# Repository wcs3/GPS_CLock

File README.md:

# GPS_CLock

A device that displays time and date on 7-segment displays in ISO8601 format.

Features:
 - Retrieves accurate time from GPS satellites
 - Displays time in compliance with ISO8601
 - Powered from a rechargeable battery for portable usage
 - Charges from a power delivery capable USB Type-C port

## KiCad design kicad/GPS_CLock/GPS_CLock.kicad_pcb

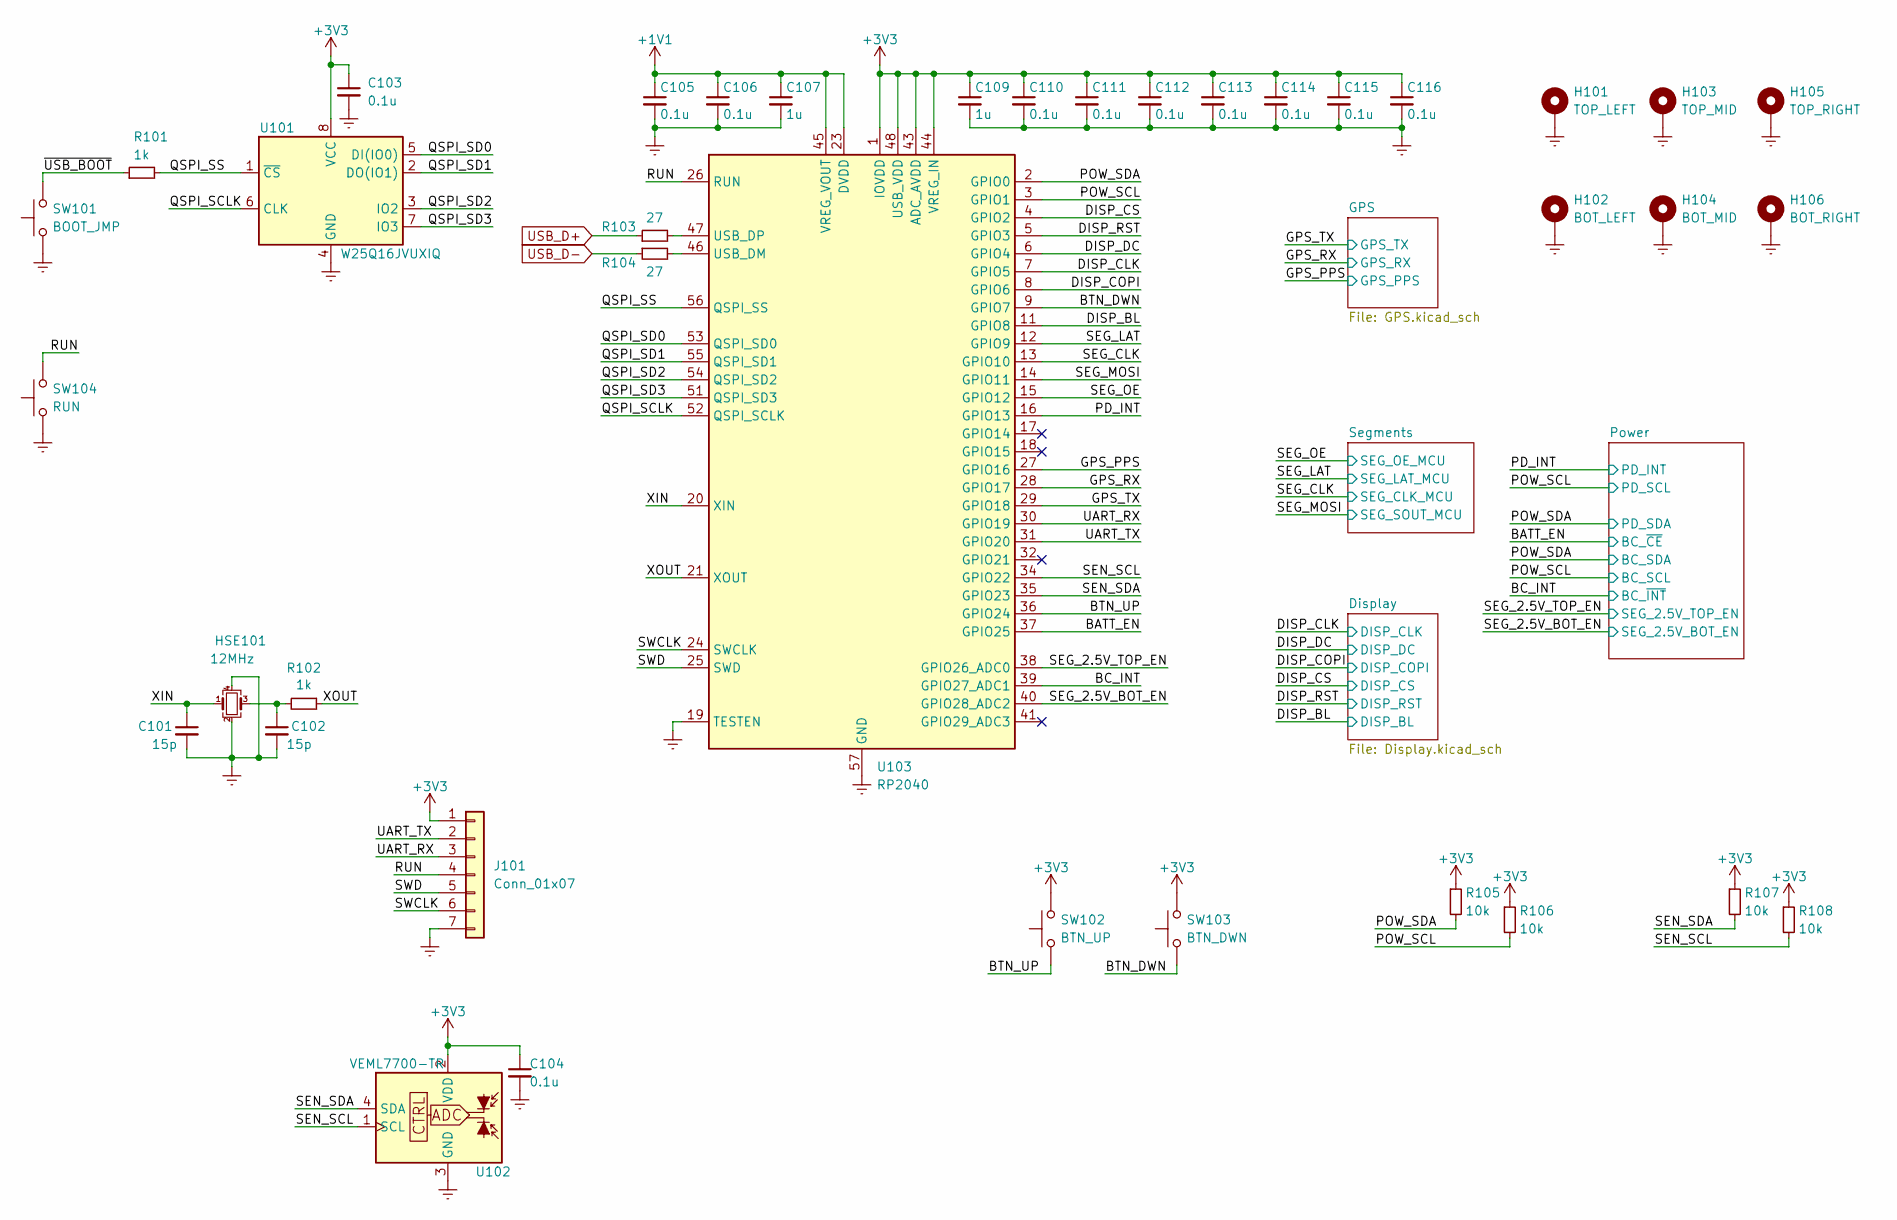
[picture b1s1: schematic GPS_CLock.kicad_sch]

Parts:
C101, C102: 15p; C_0402_1005Metric
C103, C104, C105, C106, C110, C111, C112, C113, C114, C115, C116: 0.1u; C_0402_1005Metric
C107, C109: 1u; C_0402_1005Metric
H101: TOP_LEFT; MountingHole_3.2mm_M3_DIN965_Pad
H102: BOT_LEFT; MountingHole_3.2mm_M3_DIN965_Pad
H103: TOP_MID; MountingHole_3.2mm_M3_DIN965_Pad
H104: BOT_MID; MountingHole_3.2mm_M3_DIN965_Pad
H105: TOP_RIGHT; MountingHole_3.2mm_M3_DIN965_Pad
H106: BOT_RIGHT; MountingHole_3.2mm_M3_DIN965_Pad
HSE101: 12MHz; Crystal_SMD_3225-4Pin_3.2x2.5mm
J101: Conn_01x07; PinHeader_1x07_P1.27mm_Vertical
R101, R102: 1k; R_0402_1005Metric
R103, R104: 27; R_0402_1005Metric
R105, R106, R107, R108: 10k; R_0402_1005Metric
SW101: BOOT_JMP; SW_SPST_EVQP2
SW102: BTN_UP; SW_SPST_EVQP2
SW103: BTN_DWN; SW_SPST_EVQP2
SW104: RUN; SW_SPST_EVQP2
U101: W25Q16JVUXIQ; WINBOND_USON-8_2x3mm
U102: VEML7700-TR; VEML7700
U103: RP2040; QFN-56-1EP_7x7mm_P0.4mm_EP3.2x3.2mm

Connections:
+1V1: C105.1, C106.1, C107.1, U103.23 (DVDD), U103.45 (VREG_VOUT), U103.50 (DVDD)
+3V3: C103.1, C104.1, C109.1, C110.1, C111.1, C112.1, C113.1, C114.1, C115.1, C116.1, J101.1, R105.1, R106.1, R107.1, R108.1, SW102.1, SW103.1, U101.8 (VCC), U102.2 (VDD), U103.1 (IOVDD), U103.10 (IOVDD), U103.22 (IOVDD), U103.33 (IOVDD), U103.42 (IOVDD), U103.43 (ADC_AVDD), U103.44 (VREG_IN), U103.48 (USB_VDD), U103.49 (IOVDD); also elsewhere on the board
/BATT_EN: U103.37 (GPIO25); also elsewhere on the board
/BC_INT: U103.39 (GPIO27_ADC1); also elsewhere on the board
/BTN_DWN: SW103.2, U103.9 (GPIO7)
/BTN_UP: SW102.2, U103.36 (GPIO24)
/DISP_BL: U103.11 (GPIO8); also elsewhere on the board
/DISP_CLK: U103.7 (GPIO5); also elsewhere on the board
/DISP_COPI: U103.8 (GPIO6); also elsewhere on the board
/DISP_CS: U103.4 (GPIO2); also elsewhere on the board
/DISP_DC: U103.6 (GPIO4); also elsewhere on the board
/DISP_RST: U103.5 (GPIO3); also elsewhere on the board
/GPS_PPS: U103.27 (GPIO16); also elsewhere on the board
/GPS_RX: U103.28 (GPIO17); also elsewhere on the board
/GPS_TX: U103.29 (GPIO18); also elsewhere on the board
/PD_INT: U103.16 (GPIO13); also elsewhere on the board
/POW_SCL: R106.2, U103.3 (GPIO1); also elsewhere on the board
/POW_SDA: R105.2, U103.2 (GPIO0); also elsewhere on the board
/QSPI_SCLK: U101.6 (CLK), U103.52 (QSPI_SCLK)
/QSPI_SD0: U101.5 (DI(IO0)), U103.53 (QSPI_SD0)
/QSPI_SD1: U101.2 (DO(IO1)), U103.55 (QSPI_SD1)
/QSPI_SD2: U101.3 (IO2), U103.54 (QSPI_SD2)
/QSPI_SD3: U101.7 (IO3), U103.51 (QSPI_SD3)
/QSPI_SS: R101.2, U101.1 (~CS), U103.56 (QSPI_SS)
/RUN: J101.4, SW104.1, U103.26 (RUN)
/SEG_2.5V_BOT_EN: U103.40 (GPIO28_ADC2); also elsewhere on the board
/SEG_2.5V_TOP_EN: U103.38 (GPIO26_ADC0); also elsewhere on the board
/SEG_CLK: U103.13 (GPIO10); also elsewhere on the board
/SEG_LAT: U103.12 (GPIO9); also elsewhere on the board
/SEG_MOSI: U103.14 (GPIO11); also elsewhere on the board
/SEG_OE: U103.15 (GPIO12); also elsewhere on the board
/SEN_SCL: R108.2, U102.1 (SCL), U103.34 (GPIO22)
/SEN_SDA: R107.2, U102.4 (SDA), U103.35 (GPIO23)
/SWCLK: J101.6, U103.24 (SWCLK)
/SWD: J101.5, U103.25 (SWD)
/UART_RX: J101.3, U103.30 (GPIO19)
/UART_TX: J101.2, U103.31 (GPIO20)
/XIN: C101.1, HSE101.1, U103.20 (XIN)
/XOUT: R102.1, U103.21 (XOUT)
/~USB_BOOT: R101.1, SW101.1
Earth: C101.2, C102.2, C103.2, C104.2, C105.2, C106.2, C107.2, C109.2, C110.2, C111.2, C112.2, C113.2, C114.2, C115.2, C116.2, H101.1, H102.1, H103.1, H104.1, H105.1, H106.1, HSE101.2, HSE101.4, J101.7, SW101.2, SW104.2, U101.4 (GND), U102.3 (GND), U103.19 (TESTEN), U103.57 (GND); also elsewhere on the board
unnamed: C102.1, HSE101.3, R102.2
unnamed: R103.2, U103.47 (USB_DP)
unnamed: R104.2, U103.46 (USB_DM)
USB_D+: R103.1; also elsewhere on the board
USB_D-: R104.1; also elsewhere on the board

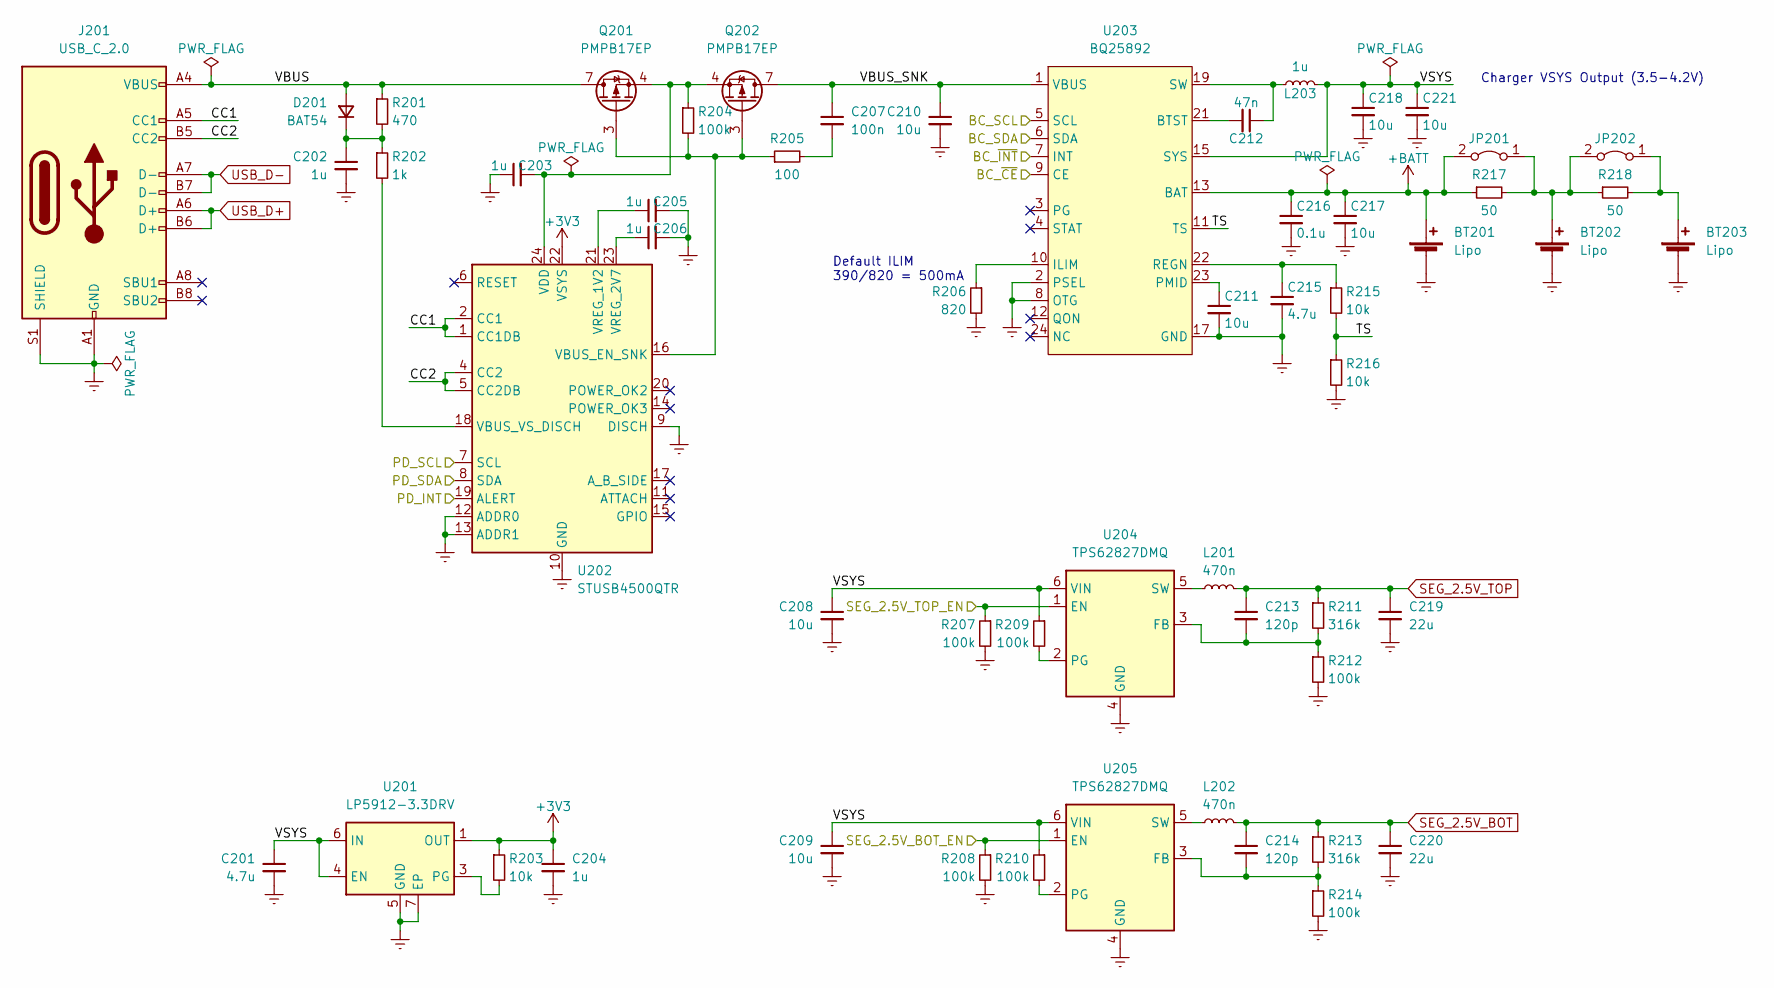
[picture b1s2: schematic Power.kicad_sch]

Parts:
BT201, BT202, BT203: Lipo; JST_PH_S2B-PH-K_1x02_P2.00mm_Horizontal
C201: 4.7u; C_0603_1608Metric
C202, C203, C204, C205, C206: 1u; C_0402_1005Metric
C207: 100n; C_0402_1005Metric
C208, C209, C217, C218, C221: 10u; C_0603_1608Metric
C210, C211: 10u; C_0402_1005Metric
C212: 47n; C_0402_1005Metric
C213, C214: 120p; C_0402_1005Metric
C215: 4.7u; C_0402_1005Metric
C216: 0.1u; C_0402_1005Metric
C219, C220: 22u; C_0603_1608Metric
D201: BAT54; D_SOD-323
J201: USB_C_2.0; USB_C_Receptacle_JAE_DX07S016JA1R1500
JP201, JP202: Jumper_2_Bridged; PinHeader_1x02_P2.54mm_Horizontal
L201, L202: 470n; L_DFE201610
L203: 1u; L_Vishay_IHLP-2020
Q201, Q202: PMPB17EP; NXP_DFN6_2.0x2.0mm 2xEp
R201: 470; R_0402_1005Metric
R202: 1k; R_0402_1005Metric
R203, R215, R216: 10k; R_0402_1005Metric
R204, R207, R208, R209, R210, R212, R214: 100k; R_0402_1005Metric
R205: 100; R_0402_1005Metric
R206: 820; R_0402_1005Metric
R211, R213: 316k; R_0402_1005Metric
R217, R218: 50; R_1206_3216Metric
U201: LP5912-3.3DRV; WSON-6-1EP_2x2mm_P0.65mm_EP1x1.6mm_ThermalVias
U202: STUSB4500QTR; QFN-24-1EP_4x4mm_P0.5mm_EP2.7x2.7mm
U203: BQ25892; Texas_S-PWQFN-N24_EP2.7x2.7mm
U204, U205: TPS62827DMQ; VSON-6-HR

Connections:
+3V3: C204.1, R203.1, U201.1 (OUT), U202.22 (VSYS); also elsewhere on the board
+BATT: BT201.1 (+), C216.1, C217.1, JP201.2 (B), R217.1, U203.13 (BAT), U203.14 (BAT)
/BATT_EN: U203.9 (CE); also elsewhere on the board
/BC_INT: U203.7 (INT); also elsewhere on the board
/PD_INT: U202.19 (ALERT); also elsewhere on the board
/POW_SCL: U202.7 (SCL), U203.5 (SCL); also elsewhere on the board
/POW_SDA: U202.8 (SDA), U203.6 (SDA); also elsewhere on the board
/Power/CC1: J201.A5 (CC1), U202.1 (CC1DB), U202.2 (CC1)
/Power/CC2: J201.B5 (CC2), U202.4 (CC2), U202.5 (CC2DB)
/Power/TS: R215.2, R216.1, U203.11 (TS)
/Power/VBUS: D201.2 (A), J201.A4 (VBUS), J201.A9 (VBUS), J201.B4 (VBUS), J201.B9 (VBUS), Q201.1 (D), Q201.2 (D), Q201.5 (D), Q201.6 (D), Q201.7 (D), R201.1
/Power/VBUS_SNK: C207.1, C210.1, Q202.1 (D), Q202.2 (D), Q202.5 (D), Q202.6 (D), Q202.7 (D), U203.1 (VBUS)
/Power/VSYS: C201.1, C208.1, C209.1, C218.1, C221.1, L203.2, R209.1, R210.1, U201.4 (EN), U201.6 (IN), U203.15 (SYS), U203.16 (SYS), U204.6 (VIN), U205.6 (VIN)
/SEG_2.5V_BOT_EN: R208.1, U205.1 (EN); also elsewhere on the board
/SEG_2.5V_TOP_EN: R207.1, U204.1 (EN); also elsewhere on the board
Earth: BT201.2 (-), BT202.2 (-), BT203.2 (-), C201.2, C202.2, C203.1, C204.2, C205.2, C206.2, C208.2, C209.2, C210.2, C211.2, C215.2, C216.2, C217.2, C218.2, C219.2, C220.2, C221.2, J201.A1 (GND), J201.A12 (GND), J201.B1 (GND), J201.B12 (GND), J201.S1 (SHIELD), R206.2, R207.2, R208.2, R212.2, R214.2, R216.2, U201.5 (GND), U201.7 (EP), U202.9 (DISCH), U202.10 (GND), U202.12 (ADDR0), U202.13 (ADDR1), U202.25 (GND), U203.2 (PSEL), U203.8 (OTG), U203.17 (GND), U203.18 (GND), U203.25 (GND), U204.4 (GND), U205.4 (GND); also elsewhere on the board
unnamed: BT202.1 (+), JP201.1 (A), JP202.2 (B), R217.2, R218.1
unnamed: BT203.1 (+), JP202.1 (A), R218.2
unnamed: C202.1, D201.1 (K), R201.2, R202.1
unnamed: C203.2, Q201.4 (S), Q201.8 (S), Q202.4 (S), Q202.8 (S), R204.1, U202.24 (VDD)
unnamed: C205.1, U202.21 (VREG_1V2)
unnamed: C206.1, U202.23 (VREG_2V7)
unnamed: C207.2, R205.2
unnamed: C211.1, U203.23 (PMID)
unnamed: C212.1, L203.1, U203.19 (SW), U203.20 (SW)
unnamed: C212.2, U203.21 (BTST)
unnamed: C213.2, R211.2, R212.1, U204.3 (FB)
unnamed: C214.2, R213.2, R214.1, U205.3 (FB)
unnamed: C215.1, R215.1, U203.22 (REGN)
unnamed: L201.1, U204.5 (SW)
unnamed: L202.1, U205.5 (SW)
unnamed: Q201.3 (G), Q202.3 (G), R204.2, R205.1, U202.16 (VBUS_EN_SNK)
unnamed: R202.2, U202.18 (VBUS_VS_DISCH)
unnamed: R203.2, U201.3 (PG)
unnamed: R206.1, U203.10 (ILIM)
unnamed: R209.2, U204.2 (PG)
unnamed: R210.2, U205.2 (PG)
SEG_2.5V_BOT: C214.1, C220.1, L202.2, R213.1; also elsewhere on the board
SEG_2.5V_TOP: C213.1, C219.1, L201.2, R211.1; also elsewhere on the board
USB_D+: J201.A6 (D+), J201.B6 (D+); also elsewhere on the board
USB_D-: J201.A7 (D-), J201.B7 (D-); also elsewhere on the board

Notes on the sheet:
Default ILIM 390/820 = 500mA
Charger VSYS Output (3.5-4.2V)

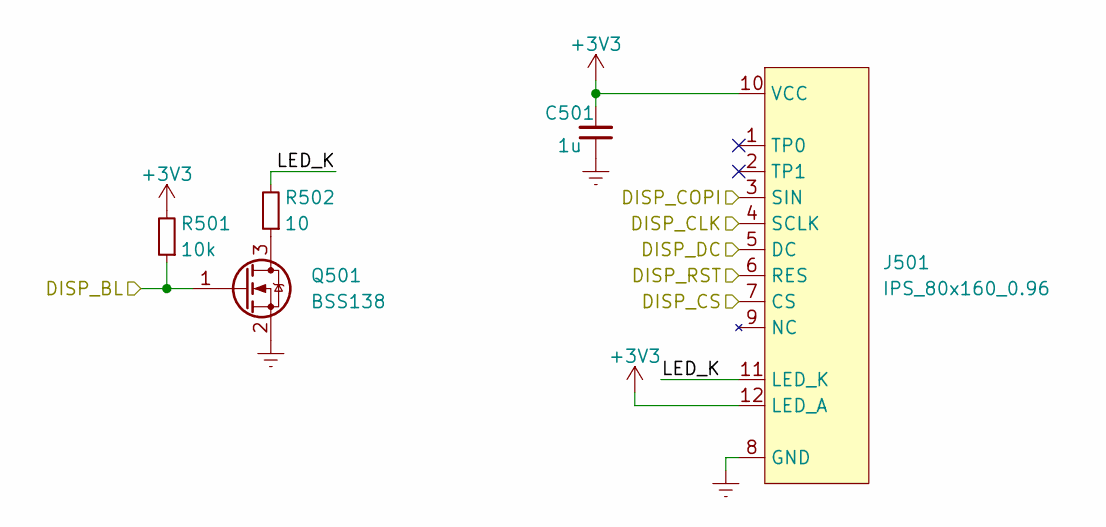
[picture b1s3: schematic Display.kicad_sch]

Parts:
C501: 1u; C_0402_1005Metric
J501: IPS_80x160_0.96; IPS_FPC-13
Q501: BSS138; SOT-23
R501: 10k; R_0402_1005Metric
R502: 10; R_0402_1005Metric

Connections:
+3V3: C501.2, J501.10 (VCC), J501.12 (LED_A), R501.2; also elsewhere on the board
/DISP_BL: Q501.1 (G), R501.1; also elsewhere on the board
/DISP_CLK: J501.4 (SCLK); also elsewhere on the board
/DISP_COPI: J501.3 (SIN); also elsewhere on the board
/DISP_CS: J501.7 (CS); also elsewhere on the board
/DISP_DC: J501.5 (DC); also elsewhere on the board
/DISP_RST: J501.6 (RES); also elsewhere on the board
/Display/LED_K: J501.11 (LED_K), R502.2
Earth: C501.1, J501.8 (GND), J501.13 (GND), Q501.2 (S); also elsewhere on the board
unnamed: Q501.3 (D), R502.1
